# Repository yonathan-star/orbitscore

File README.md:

# OrbitScore

A tabletop percussion sequencer that reads interchangeable perforated rhythm discs. One disc stores sixteen steps across four tracks: kick, snare, hi-hat, and tom. Turn the disc by hand to scan the pattern; a Raspberry Pi Pico then loops it at an independent electronic tempo.

## Design

Six optical channels read four data tracks, a clock track, and an index marker. Separate controller, reader, and emitter boards connect the optical scanner to the Pico. A MAX98357A amplifier drives a speaker. Two knobs set tempo and gain; four track mutes control the arrangement.

The 164 mm disc fits a 190 × 190 mm scanner enclosure. The controls occupy a separate 110 × 110 mm pod. The firmware synthesizes the four percussion voices mathematically.

## Files

- `hardware/`: editable KiCad schematics, layouts, local footprints, Gerbers, and drill files for all three boards.
- `mechanical/`: OpenSCAD source, individual printable STL parts, and board STEP references.
- `firmware/`: MicroPython scanner, sequencer, and percussion synthesis.
- `bom.csv`: component list with researched prices and explicitly marked allowances.
- `docs/`: design specifications, assembly wiring, budget, and bring-up procedure.
- `verification/`: firmware and board-check reports.

## Validation and next steps

The supplied reports record nine desktop firmware tests passed, 159 matching schematic/PCB pin assignments, zero unconnected pads, and zero electrical DRC errors. These checks validate files and software logic. The physical assembly, optical sensitivity, ambient-light immunity, Pico audio timing, and printed fit remain untested.

Before fabrication, check purchased component footprints, optical polarity/current, enclosure clearances, and the final vendor carts. The BOM includes procurement allowances and is not a delivered-price quote.

## Opening the project

Open `hardware/controller/controller.kicad_pro` in KiCad 7 or newer. Open `mechanical/orbitscore.scad` in OpenSCAD. See `docs/wiring-and-assembly.txt` and `docs/bring-up.txt` before connecting hardware.

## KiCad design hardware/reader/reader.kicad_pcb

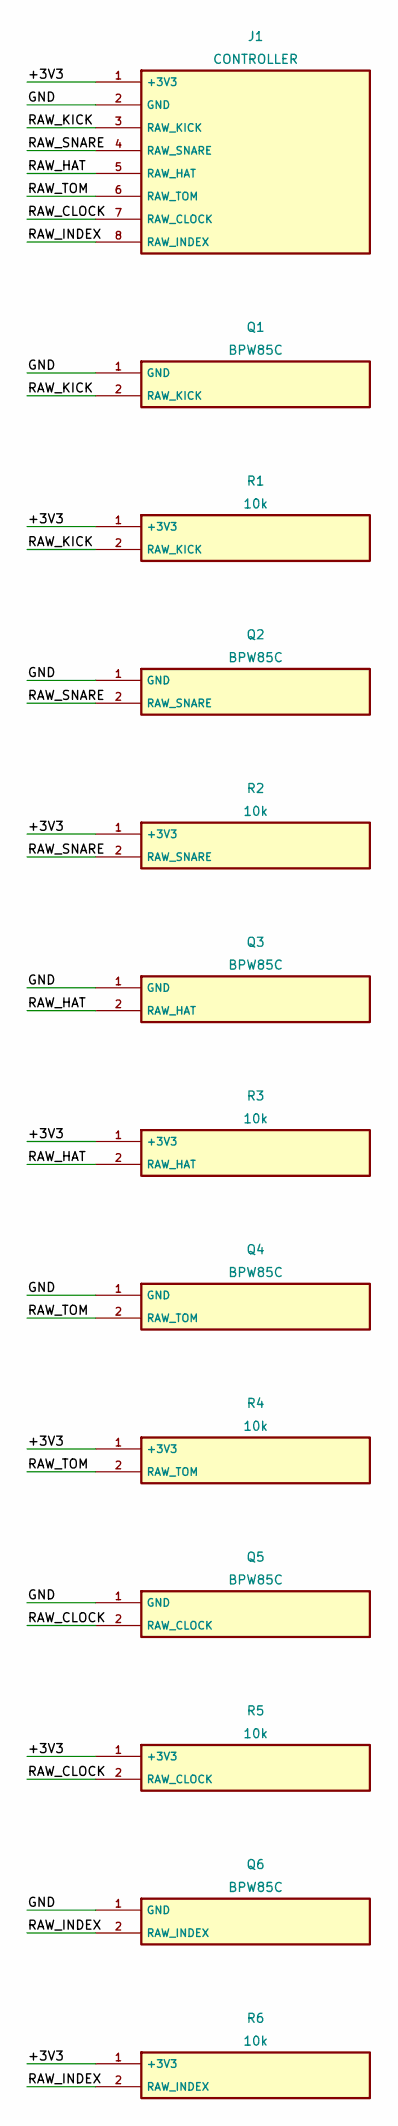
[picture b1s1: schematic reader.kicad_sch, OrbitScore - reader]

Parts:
J1: CONTROLLER; PinHeader_2x04_P2.54mm_Vertical
Q1, Q2, Q3, Q4, Q5, Q6: BPW85C
R1, R2, R3, R4, R5, R6: 10k; R_Axial_DIN0207_L6.3mm_D2.5mm_P10.16mm_Horizontal

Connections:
+3V3: J1.1 (+3V3), R1.1 (+3V3), R2.1 (+3V3), R3.1 (+3V3), R4.1 (+3V3), R5.1 (+3V3), R6.1 (+3V3)
GND: J1.2 (GND), Q1.1 (GND), Q2.1 (GND), Q3.1 (GND), Q4.1 (GND), Q5.1 (GND), Q6.1 (GND)
RAW_CLOCK: J1.7 (RAW_CLOCK), Q5.2 (RAW_CLOCK), R5.2 (RAW_CLOCK)
RAW_HAT: J1.5 (RAW_HAT), Q3.2 (RAW_HAT), R3.2 (RAW_HAT)
RAW_INDEX: J1.8 (RAW_INDEX), Q6.2 (RAW_INDEX), R6.2 (RAW_INDEX)
RAW_KICK: J1.3 (RAW_KICK), Q1.2 (RAW_KICK), R1.2 (RAW_KICK)
RAW_SNARE: J1.4 (RAW_SNARE), Q2.2 (RAW_SNARE), R2.2 (RAW_SNARE)
RAW_TOM: J1.6 (RAW_TOM), Q4.2 (RAW_TOM), R4.2 (RAW_TOM)

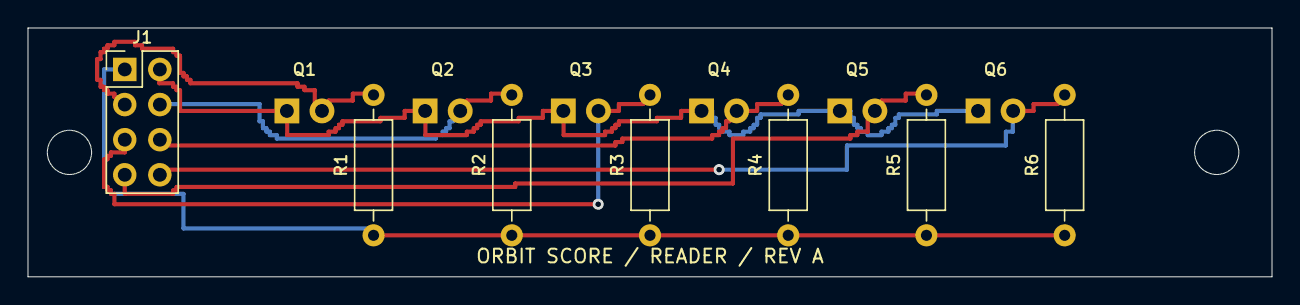
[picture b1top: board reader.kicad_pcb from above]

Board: 2 copper layers, 90.0 x 18.0 mm, 15 parts (0 on the bottom side), 8 nets.

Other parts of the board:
H39, H869: MountingHole_3.2mm

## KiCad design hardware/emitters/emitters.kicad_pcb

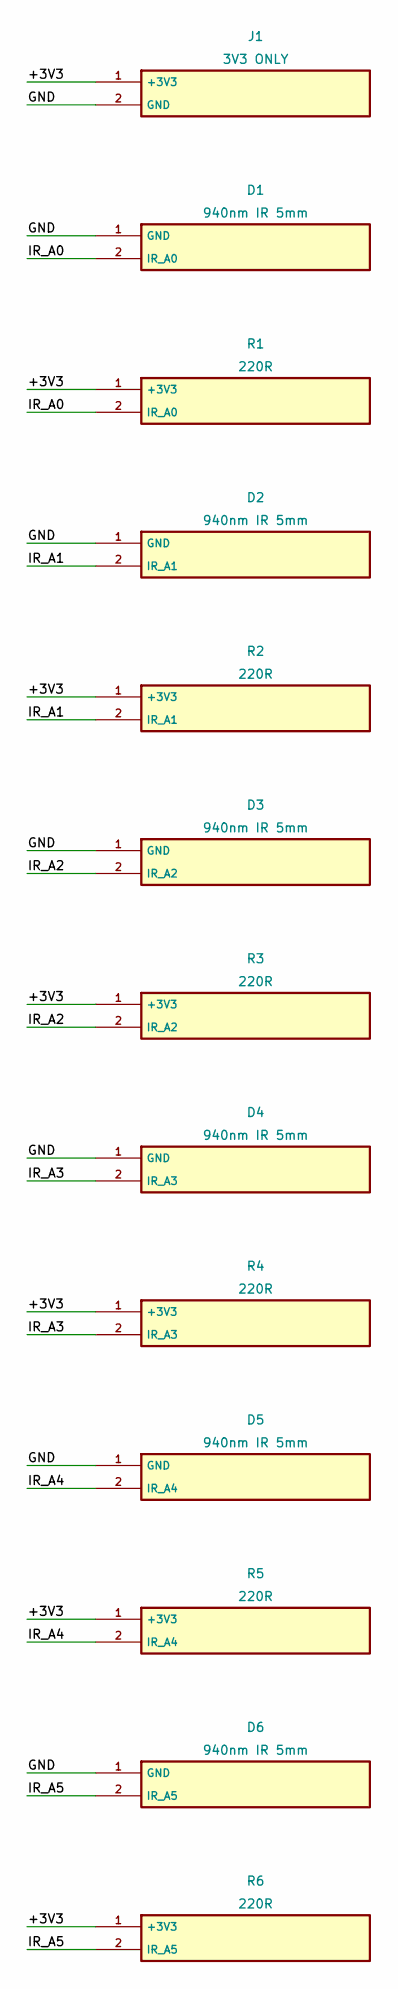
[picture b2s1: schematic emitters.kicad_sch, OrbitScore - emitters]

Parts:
D1, D2, D3, D4, D5, D6: 940nm IR 5mm; IR_5mm
J1: 3V3 ONLY; PinHeader_1x02_P2.54mm_Vertical
R1, R2, R3, R4, R5, R6: 220R; R_Axial_DIN0207_L6.3mm_D2.5mm_P10.16mm_Horizontal

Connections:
+3V3: J1.1 (+3V3), R1.1 (+3V3), R2.1 (+3V3), R3.1 (+3V3), R4.1 (+3V3), R5.1 (+3V3), R6.1 (+3V3)
GND: D1.1 (GND), D2.1 (GND), D3.1 (GND), D4.1 (GND), D5.1 (GND), D6.1 (GND), J1.2 (GND)
IR_A0: D1.2 (IR_A0), R1.2 (IR_A0)
IR_A1: D2.2 (IR_A1), R2.2 (IR_A1)
IR_A2: D3.2 (IR_A2), R3.2 (IR_A2)
IR_A3: D4.2 (IR_A3), R4.2 (IR_A3)
IR_A4: D5.2 (IR_A4), R5.2 (IR_A4)
IR_A5: D6.2 (IR_A5), R6.2 (IR_A5)

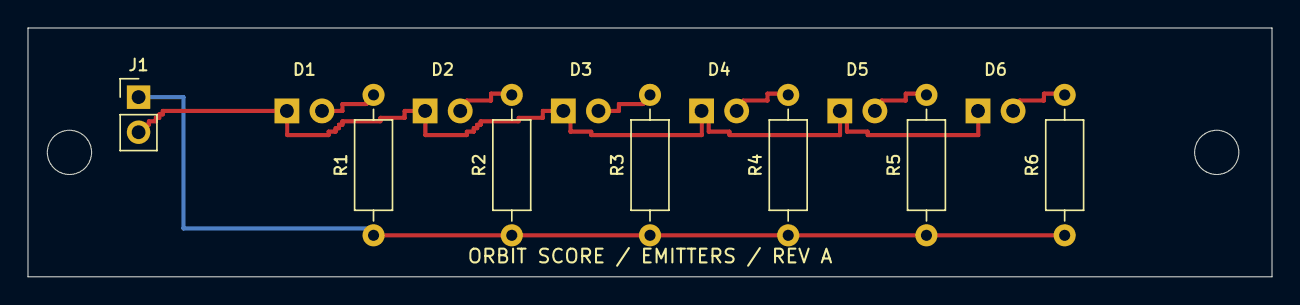
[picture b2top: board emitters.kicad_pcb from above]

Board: 2 copper layers, 90.0 x 18.0 mm, 15 parts (0 on the bottom side), 8 nets.

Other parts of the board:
H39, H869: MountingHole_3.2mm

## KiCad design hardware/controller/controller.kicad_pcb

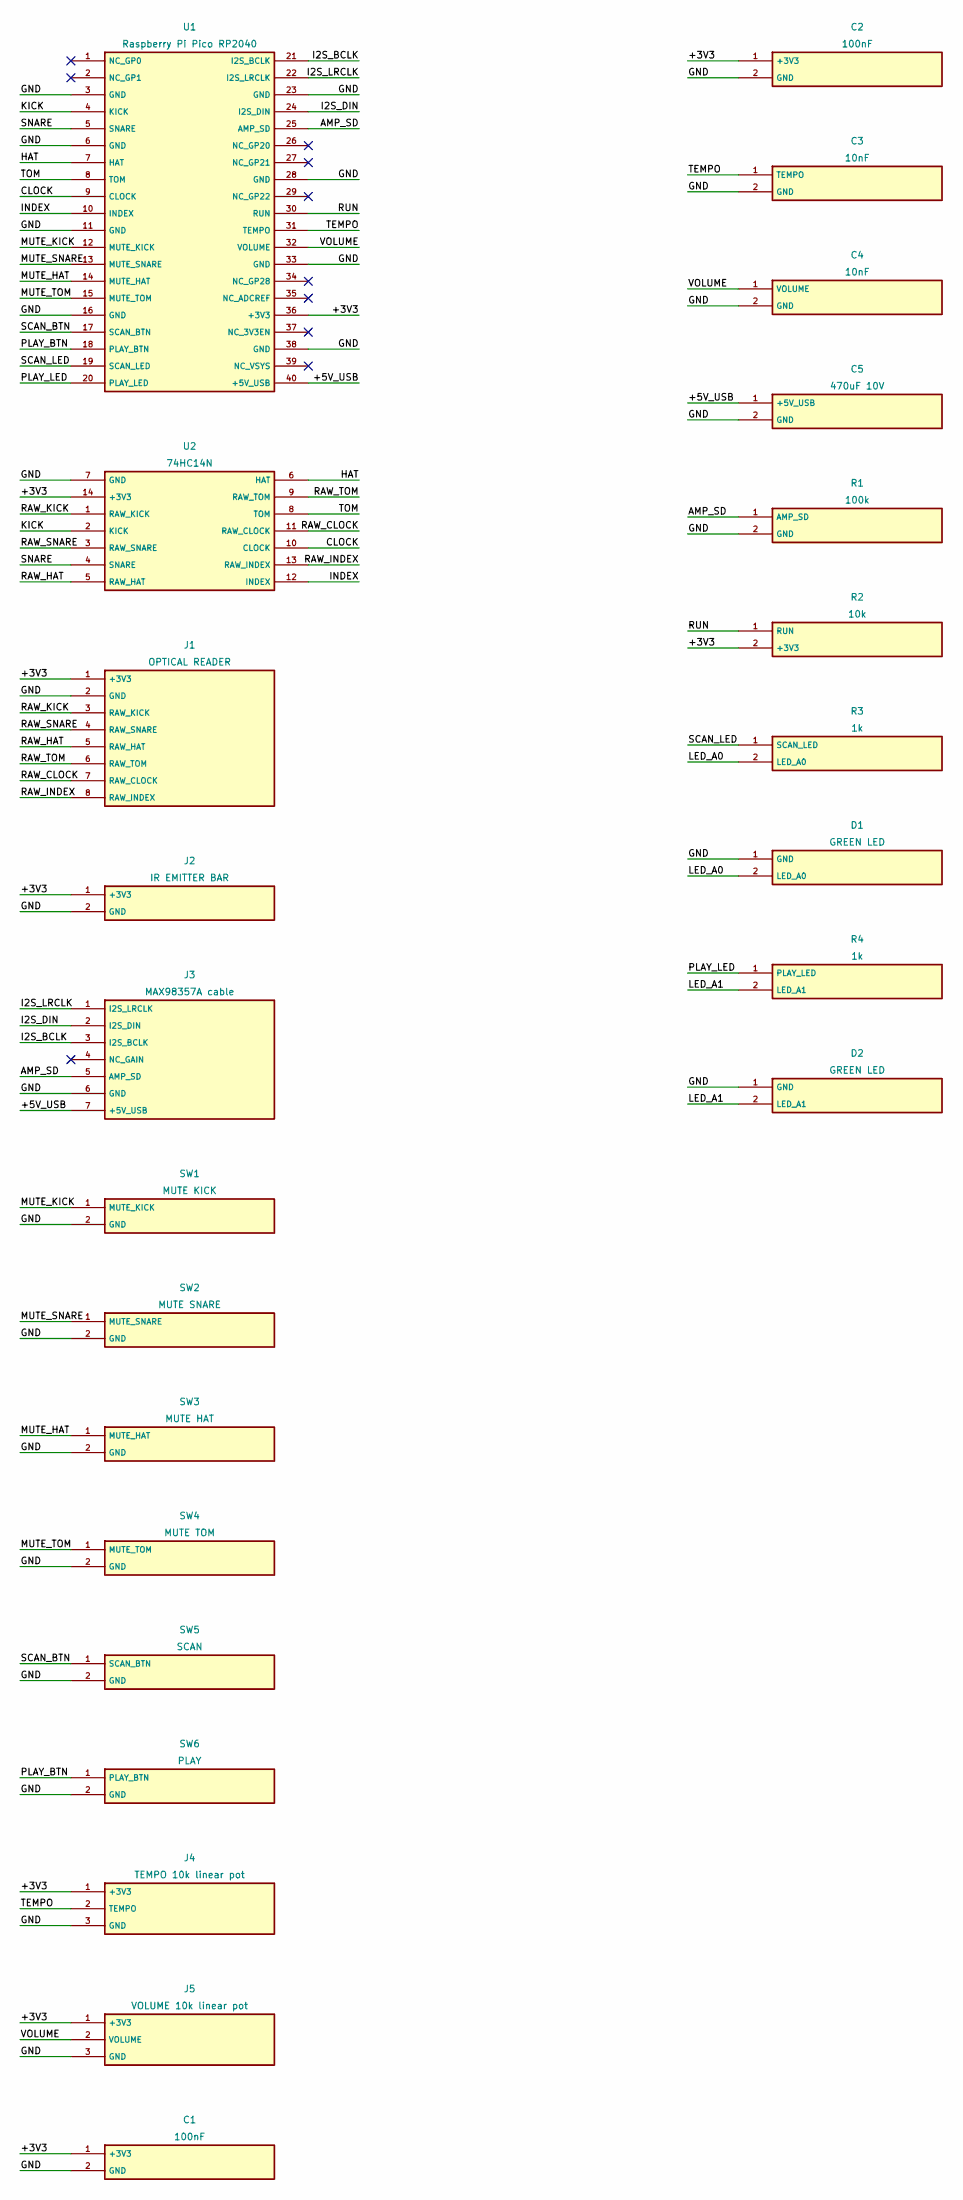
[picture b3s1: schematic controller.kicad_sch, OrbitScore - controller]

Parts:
C1, C2: 100nF; C_Disc_D5.0mm_W2.5mm_P5.00mm
C3, C4: 10nF; C_Disc_D5.0mm_W2.5mm_P5.00mm
C5: 470uF 10V; CP_Radial_D8.0mm_P3.50mm
D1, D2: GREEN LED; LED_D3.0mm
J1: OPTICAL READER; PinHeader_1x08_P2.54mm_Vertical
J2: IR EMITTER BAR; PinHeader_1x02_P2.54mm_Vertical
J3: MAX98357A cable; PinHeader_1x07_P2.54mm_Vertical
J4: TEMPO 10k linear pot; PinHeader_1x03_P2.54mm_Vertical
J5: VOLUME 10k linear pot; PinHeader_1x03_P2.54mm_Vertical
R1: 100k; R_Axial_DIN0207_L6.3mm_D2.5mm_P10.16mm_Horizontal
R2: 10k; R_Axial_DIN0207_L6.3mm_D2.5mm_P10.16mm_Horizontal
R3, R4: 1k; R_Axial_DIN0207_L6.3mm_D2.5mm_P10.16mm_Horizontal
SW1: MUTE KICK; Button_6mm
SW2: MUTE SNARE; Button_6mm
SW3: MUTE HAT; Button_6mm
SW4: MUTE TOM; Button_6mm
SW5: SCAN; Button_6mm
SW6: PLAY; Button_6mm
U1: Raspberry Pi Pico RP2040; Pico_Socket
U2: 74HC14N; DIP-14_W7.62mm

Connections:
+3V3: C1.1 (+3V3), C2.1 (+3V3), J1.1 (+3V3), J2.1 (+3V3), J4.1 (+3V3), J5.1 (+3V3), R2.2 (+3V3), U1.36 (+3V3), U2.14 (+3V3)
+5V_USB: C5.1 (+5V_USB), J3.7 (+5V_USB), U1.40 (+5V_USB)
AMP_SD: J3.5 (AMP_SD), R1.1 (AMP_SD), U1.25 (AMP_SD)
CLOCK: U1.9 (CLOCK), U2.10 (CLOCK)
GND: C1.2 (GND), C2.2 (GND), C3.2 (GND), C4.2 (GND), C5.2 (GND), D1.1 (GND), D2.1 (GND), J1.2 (GND), J2.2 (GND), J3.6 (GND), J4.3 (GND), J5.3 (GND), R1.2 (GND), SW1.2 (GND), SW2.2 (GND), SW3.2 (GND), SW4.2 (GND), SW5.2 (GND), SW6.2 (GND), U1.3 (GND), U1.6 (GND), U1.11 (GND), U1.16 (GND), U1.23 (GND), U1.28 (GND), U1.33 (GND), U1.38 (GND), U2.7 (GND)
HAT: U1.7 (HAT), U2.6 (HAT)
I2S_BCLK: J3.3 (I2S_BCLK), U1.21 (I2S_BCLK)
I2S_DIN: J3.2 (I2S_DIN), U1.24 (I2S_DIN)
I2S_LRCLK: J3.1 (I2S_LRCLK), U1.22 (I2S_LRCLK)
INDEX: U1.10 (INDEX), U2.12 (INDEX)
KICK: U1.4 (KICK), U2.2 (KICK)
LED_A0: D1.2 (LED_A0), R3.2 (LED_A0)
LED_A1: D2.2 (LED_A1), R4.2 (LED_A1)
MUTE_HAT: SW3.1 (MUTE_HAT), U1.14 (MUTE_HAT)
MUTE_KICK: SW1.1 (MUTE_KICK), U1.12 (MUTE_KICK)
MUTE_SNARE: SW2.1 (MUTE_SNARE), U1.13 (MUTE_SNARE)
MUTE_TOM: SW4.1 (MUTE_TOM), U1.15 (MUTE_TOM)
PLAY_BTN: SW6.1 (PLAY_BTN), U1.18 (PLAY_BTN)
PLAY_LED: R4.1 (PLAY_LED), U1.20 (PLAY_LED)
RAW_CLOCK: J1.7 (RAW_CLOCK), U2.11 (RAW_CLOCK)
RAW_HAT: J1.5 (RAW_HAT), U2.5 (RAW_HAT)
RAW_INDEX: J1.8 (RAW_INDEX), U2.13 (RAW_INDEX)
RAW_KICK: J1.3 (RAW_KICK), U2.1 (RAW_KICK)
RAW_SNARE: J1.4 (RAW_SNARE), U2.3 (RAW_SNARE)
RAW_TOM: J1.6 (RAW_TOM), U2.9 (RAW_TOM)
RUN: R2.1 (RUN), U1.30 (RUN)
SCAN_BTN: SW5.1 (SCAN_BTN), U1.17 (SCAN_BTN)
SCAN_LED: R3.1 (SCAN_LED), U1.19 (SCAN_LED)
SNARE: U1.5 (SNARE), U2.4 (SNARE)
TEMPO: C3.1 (TEMPO), J4.2 (TEMPO), U1.31 (TEMPO)
TOM: U1.8 (TOM), U2.8 (TOM)
VOLUME: C4.1 (VOLUME), J5.2 (VOLUME), U1.32 (VOLUME)

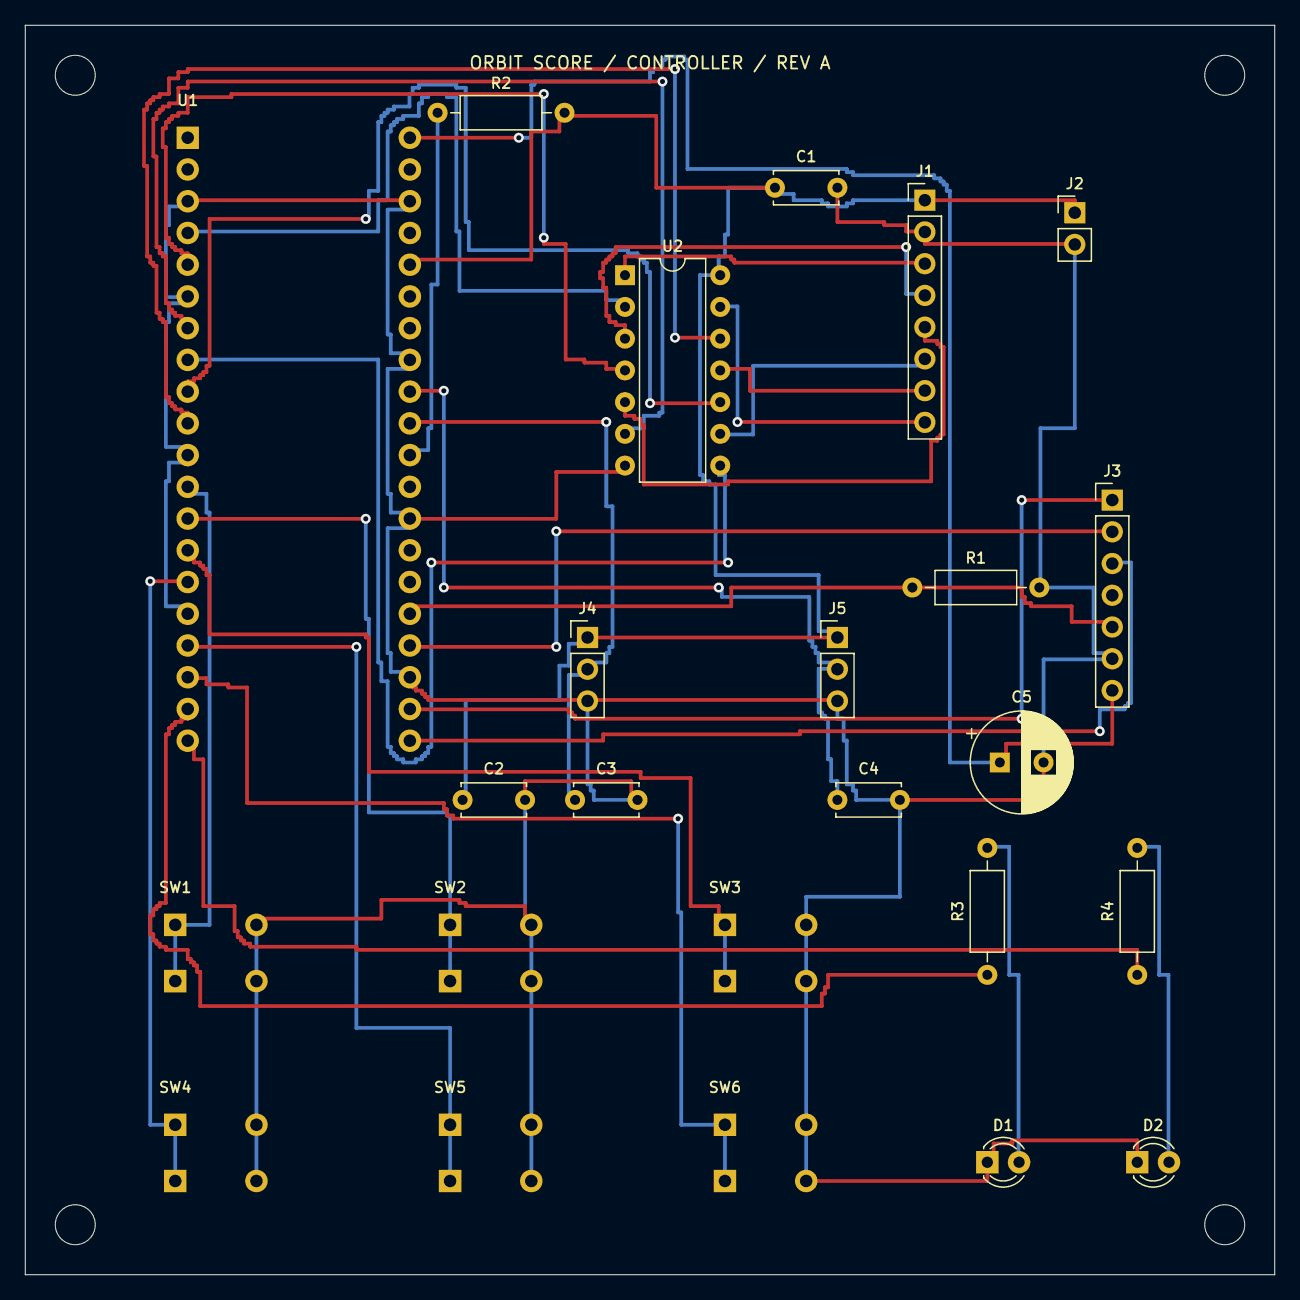
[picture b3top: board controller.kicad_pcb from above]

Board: 2 copper layers, 100.0 x 100.0 mm, 28 parts (0 on the bottom side), 32 nets.

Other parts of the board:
H44, H496, H964, H9696: MountingHole_3.2mm
